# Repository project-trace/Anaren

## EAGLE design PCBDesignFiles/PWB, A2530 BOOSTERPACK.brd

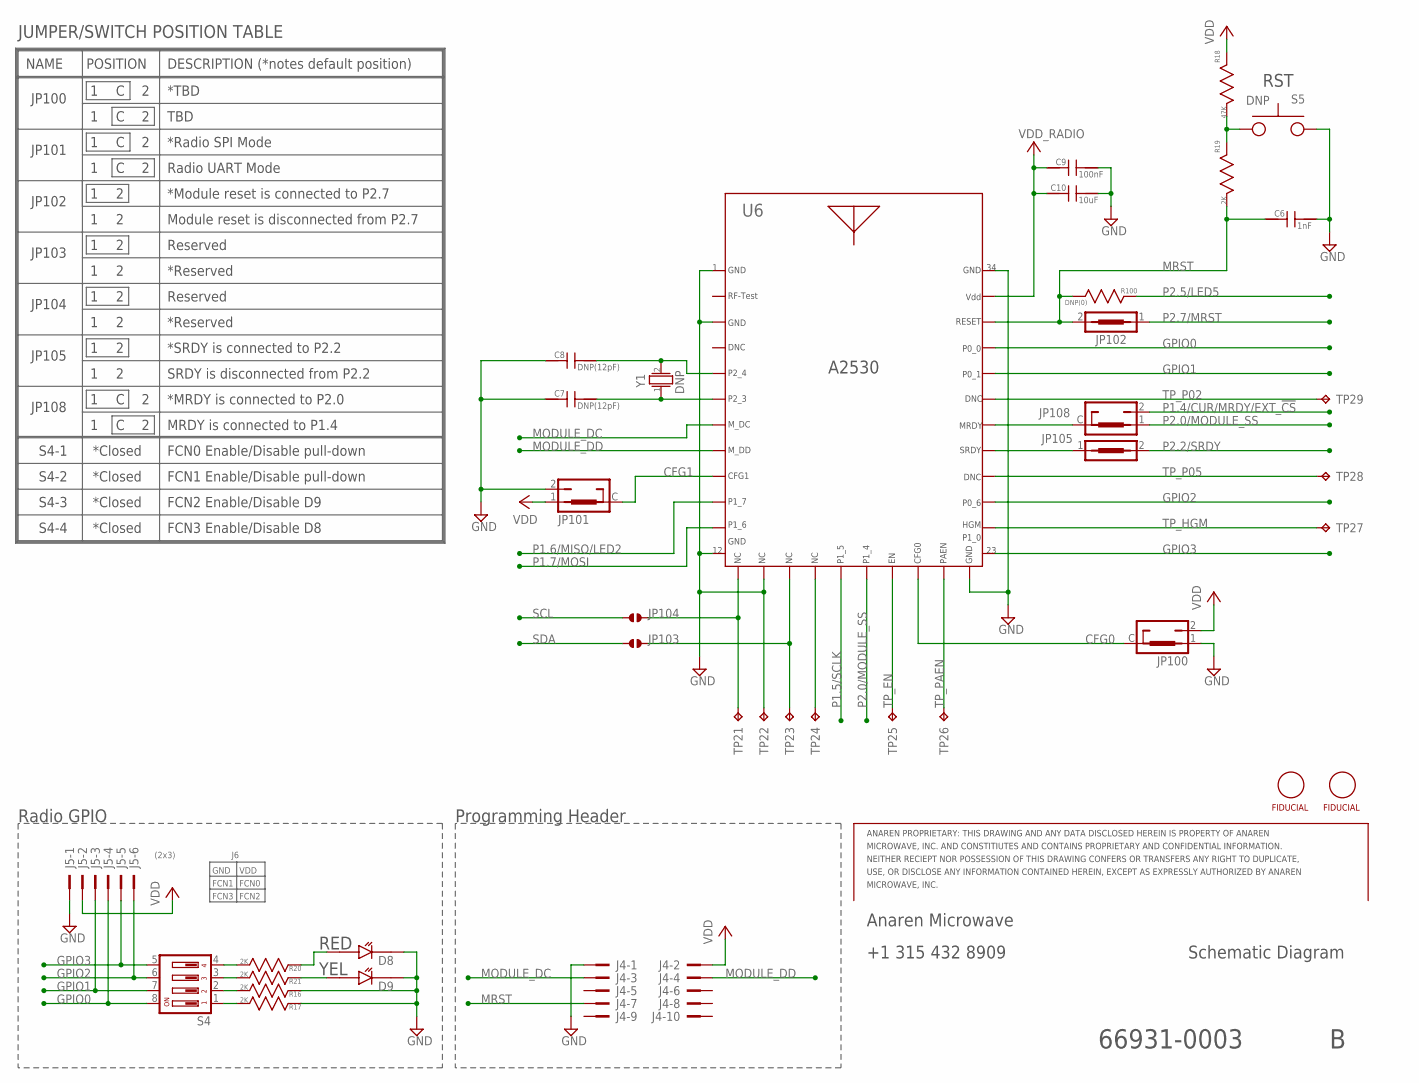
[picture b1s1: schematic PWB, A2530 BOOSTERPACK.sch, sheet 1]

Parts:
C6: 1nF; 0402CAP
C7, C8: DNP(12pF); 0402CAP
C9: 100nF; 0402CAP
C10: 10uF; 0402CAP
D8, D9: LED_SMT_0402; 0402_LED
J4: SAMTEC_SHF-105-01-L-D-TH_NO_SHROUD
J5: PROTO_100MIL_2X3
JP100, JP101, JP108: JP0603_2C_A
JP102, JP105: JP0603_1P_A
JP103, JP104: SOLDER_JUMPER_16MIL; SOLDER_JUMP_16MIL
R16, R17, R19, R20, R21: 2K; RESC1005X40N
R18: 47K; RESC1005X40N
R100: DNP(0); 0603_COMPONENT
S4: DIP_SWITCH_218-4LPSTJ
S5: DNP; SWITCH_B3U-1000P
TP21, TP22, TP23, TP24, TP25, TP26, TP27, TP28, TP29: TP_TH_20MIL_R
U6: CC2530
U$1, U$13: FIDUCIAL0.5MM; FIDUCIAL_0.5MM
Y1: DNP; ABRACON_ABS06

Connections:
CFG0: JP100.C (2), U6.20_GIO2
CFG1: JP101.C (2), U6.9_GIO13
GND: C6.P$2, C7.P$1, C8.P$1, C9.P$2, C10.P$2, D8.2, D9.2, J4.1, J5.1, JP100.1, JP101.2 (3), R16.1, R17.1, S5.2, TP22.P$1, U6.1_GND, U6.3_GND, U6.12_GND, U6.14_USBP, U6.22_GND, U6.34_GND; also elsewhere on the board
GPIO0: J5.4, S4.8, U6.31_HGM
GPIO1: J5.3, S4.7, U6.30_GND
GPIO2: J5.6, S4.6, U6.25_BCLK
GPIO3: J5.5, S4.5, U6.23_RSTN
MODULE_DC: J4.3, U6.7_SDA
MODULE_DD: J4.4, U6.8_GIO12
MRDY: JP108.C (2), U6.28_AD1
MRST: C6.P$1, J4.7, JP102.2, R19.2, R100.1, U6.32_IOVDD; also elsewhere on the board
unnamed: R20.2, S4.4
unnamed: R21.2, S4.3
unnamed: R16.2, S4.2
unnamed: R17.2, S4.1
unnamed: C7.P$2, U6.6_SCL, Y1.1
unnamed: D9.1, R21.1
unnamed: D8.1, R20.1
unnamed: JP104.P2, TP21.P$1, U6.13_USBM
unnamed: JP103.P2, TP23.P$1, U6.15_CSN
unnamed: R18.2, R19.1, S5.1
unnamed: TP24.P$1, U6.16_SCLK
P1.4/CUR/MRDY/EXT_!CS: JP108.2 (3); also elsewhere on the board
P1.5/SCLK: U6.17_MOSI; also elsewhere on the board
P1.6/MISO/LED2: U6.10_PA; also elsewhere on the board
P1.6/MISO/SCL/LED1: C8.P$2, U6.5_VBAT, Y1.2
P1.7/MOSI: U6.11_LNA; also elsewhere on the board
P2.0/MODULE_SS: JP108.1, U6.18_MISO; also elsewhere on the board
P2.2/SRDY: JP105.2; also elsewhere on the board
P2.5/LED5: R100.2; also elsewhere on the board
P2.7/MRST: JP102.1; also elsewhere on the board
SCL: JP104.P1; also elsewhere on the board
SDA: JP103.P1; also elsewhere on the board
SRDY: JP105.1, U6.27_AD0; also elsewhere on the board
TP_EN: TP25.P$1, U6.19_GIO1
TP_HGM: TP27.P$1, U6.24_MCLK
TP_P02: TP29.P$1, U6.29_GIO9/AD2
TP_P05: TP28.P$1, U6.26_WCLK
TP_PAEN: TP26.P$1, U6.21_GIO3
VDD: J4.2, J5.2, JP100.2 (3), JP101.1, R18.1; also elsewhere on the board
VDD_RADIO: C9.P$1, C10.P$1, U6.33_VDD; also elsewhere on the board

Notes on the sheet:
Schematic Diagram
Anaren Microwave
+1 315 432 8909
66931-0003
Programming Header
A2530
RST
YEL
RED
Radio GPIO
JP100
JP101
JP103
JP104
*TBD
TBD
*Radio SPI Mode
Radio UART Mode
Reserved
*Reserved
NAME
POSITION
DESCRIPTION (*notes default position)
JUMPER/SWITCH POSITION TABLE
*Closed
FCN0 Enable/Disable pull-down
S4-1
S4-2
S4-3
S4-4
FCN1 Enable/Disable pull-down
FCN2 Enable/Disable D9
FCN3 Enable/Disable D8
GND
FCN1
FCN3
FCN2
FCN0
VDD
(2x3)

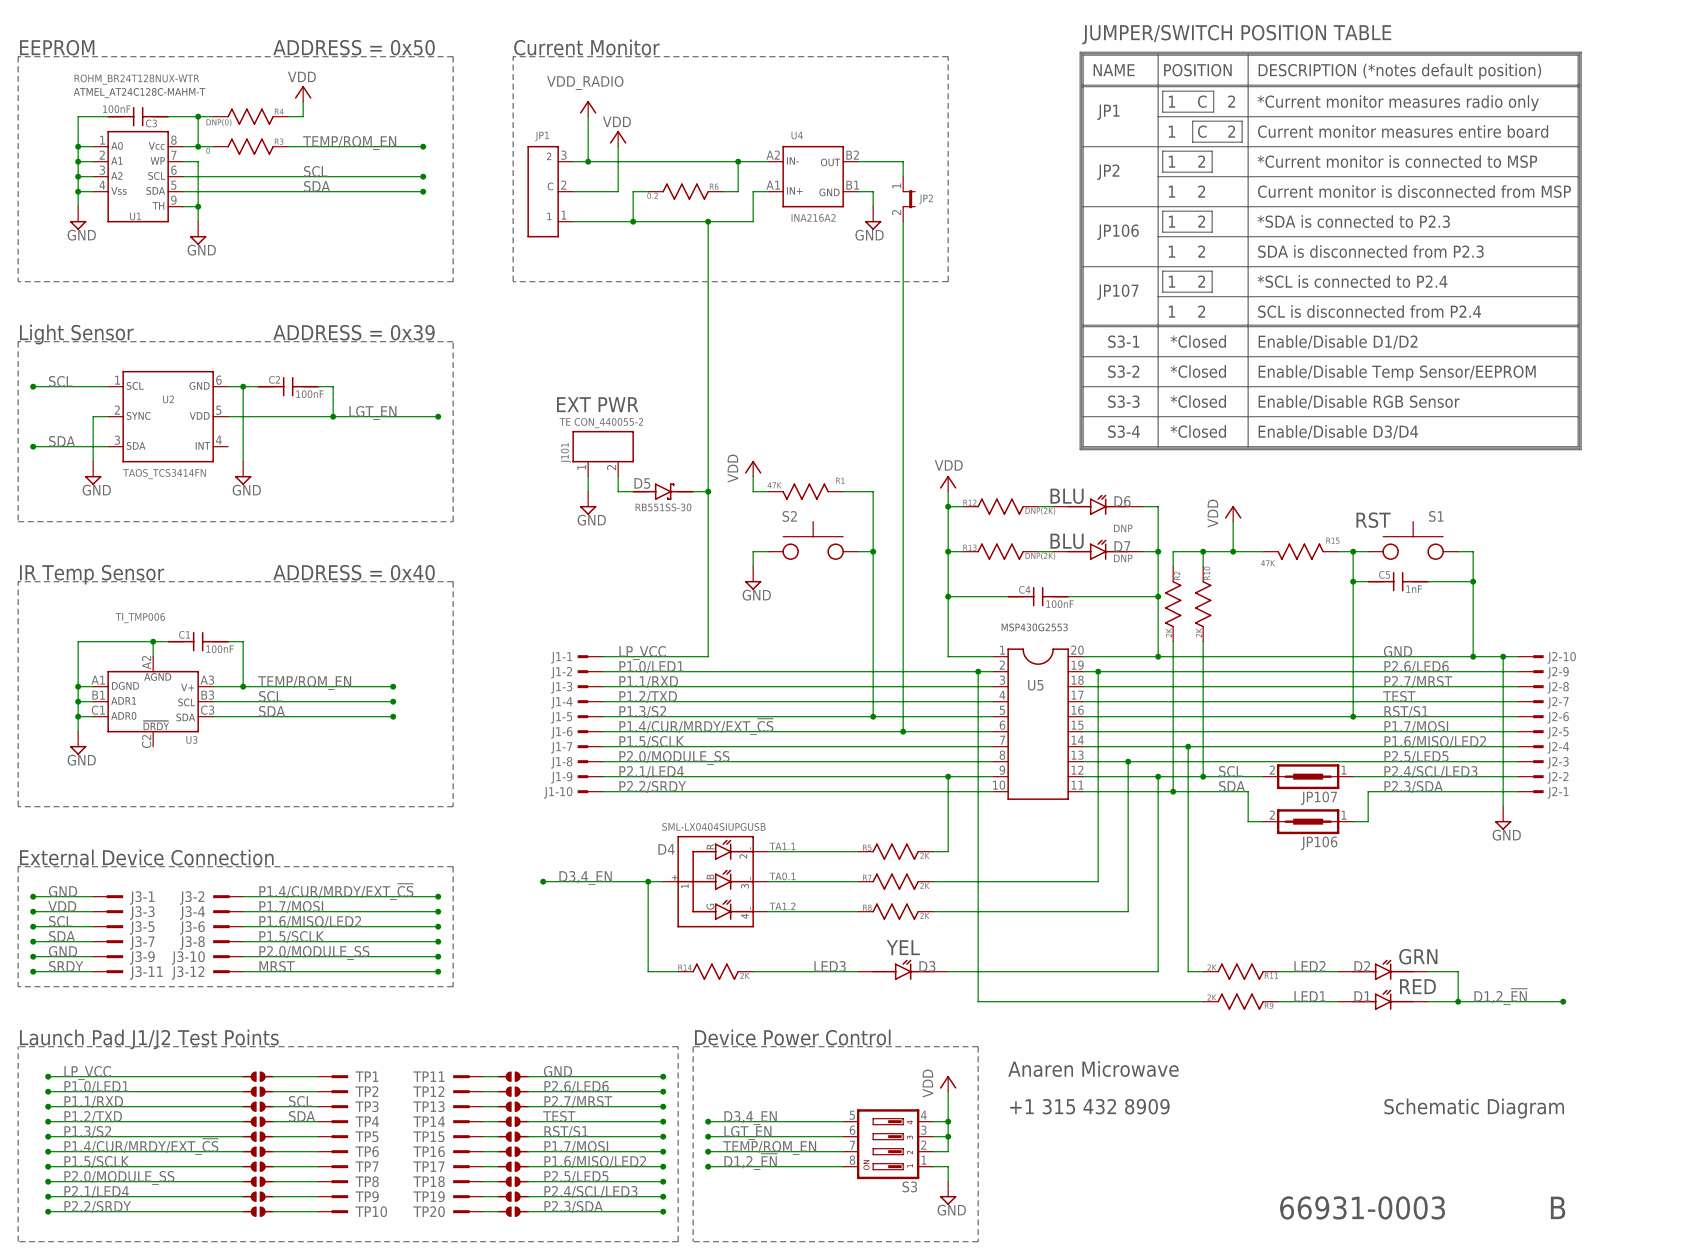
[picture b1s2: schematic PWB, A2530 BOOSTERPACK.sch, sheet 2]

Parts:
C1, C2, C3, C4: 100nF; 0402CAP
C5: 1nF; 0402CAP
D1, D2, D3, D6, D7: LED_SMT_0402; 0402_LED
D4: SML-LX0404SIUPGUSB; SML-LXO404SIUPGUSB
D5: RB551SS-30; 1608_DIODE
J1, J2: TSW-110-02-S-S
J3: PROTO_100MIL_2X6
J101: TE_CONNECTIVITY_HEADER_2POS_2MM_RIGHT_ANGLE_T/H; TE_CONNECTIVITY_HEADER_2POS_2MM_RIGHT_ANGLE_TH
JP1: SAMTEC_TMM-103-XX-X-S
JP2: 2MM_SHUNT_JUMPER; SAMTEC_TMM-102-XX-X-S
JP106, JP107: JP0603_1P_A
R1, R15: 47K; RESC1005X40N
R2, R5, R7, R8, R9, R10, R11, R14: 2K; RESC1005X40N
R3: 0; RESC1005X40N
R4: DNP(0); RESC1005X40N
R6: 0.2; RESC1005X40N
R12, R13: DNP(2K); RESC1005X40N
S1, S2: SWITCH_B3U-1000P
S3: DIP_SWITCH_218-4LPSTJ
TP1, TP2, TP3, TP4, TP5, TP6, TP7, TP8, TP9, TP10, TP11, TP12, TP13, TP14, TP15, TP16, TP17, TP18, TP19, TP20: PROTO
U1: ROHM_BR24T128NUX-WTR; UFDFN8_2.0X3.0
U2: TAOS_TCS3414FN; TAOS_DFP_3.5X2.3
U3: TI_TMP006; BGA-N8
U4: INA216A2; WCSP-4
U5: DIL20
U$2, U$3, U$4, U$5, U$6, U$7, U$8, U$9, U$10, U$11, U$14, U$15, U$16, U$17, U$18, U$19, U$20, U$21, U$22, U$23: SOLDER_JUMPER_16MIL; SOLDER_JUMP_16MIL

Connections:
CURRENT: JP2.1, U4.B2
D1,2_!EN: D1.2, D2.2, S3.8
D3,4_EN: D4.1(+), R14.1, S3.5
GND: C1.P$1, C2.P$1, C3.P$2, C4.P$2, C5.P$2, D6.2, D7.2, J2.10, J3.1, J3.9, J101.1, S1.2, S2.2, S3.1, U1.1, U1.2, U1.3, U1.4, U1.7, U1.9, U2.2, U2.6, U3.A1, U3.A2, U3.B1, U3.C1, U4.B1, U5.20, U$14.P2; also elsewhere on the board
LED1: D1.1, R9.1
LED2: D2.1, R11.1
LED3: D3.1, R14.2
LED4: D4.2(-R), R5.1
LED5: D4.4(-G), R8.1
LED6: D4.3(-B), R7.1
LGT_EN: C2.P$2, S3.6, U2.5
LP_VCC: D5.P$2, J1.1, JP1.1, R6.2, U4.A1, U$2.P1
MRST: J3.12; also elsewhere on the board
unnamed: D6.1, R12.2
unnamed: D7.1, R13.2
unnamed: C3.P$1, R3.2, R4.2, U1.8
unnamed: TP1.1, U$2.P2
unnamed: TP5.1, U$6.P2
unnamed: TP6.1, U$7.P2
unnamed: TP7.1, U$8.P2
unnamed: TP8.1, U$9.P2
unnamed: TP9.1, U$10.P2
unnamed: TP10.1, U$11.P2
unnamed: TP11.1, U$14.P1
unnamed: TP12.1, U$15.P1
unnamed: TP13.1, U$16.P1
unnamed: TP14.1, U$17.P1
unnamed: TP15.1, U$18.P1
unnamed: TP16.1, U$19.P1
unnamed: TP17.1, U$20.P1
unnamed: TP18.1, U$21.P1
unnamed: TP19.1, U$22.P1
unnamed: TP20.1, U$23.P1
unnamed: D5.P$1, J101.2
P1.0/LED1: J1.2, R9.2, U5.2, U$3.P1
P1.1/RXD: J1.3, U5.3, U$4.P1
P1.2/TXD: J1.4, U5.4, U$5.P1
P1.3/S2: J1.5, R1.1, S2.1, U5.5, U$6.P1
P1.4/CUR/MRDY/EXT_!CS: J1.6, J3.2, JP2.2, U5.6, U$7.P1; also elsewhere on the board
P1.5/SCLK: J1.7, J3.8, U5.7, U$8.P1; also elsewhere on the board
P1.6/MISO/LED2: J2.4, J3.6, R11.2, U5.14, U$20.P2; also elsewhere on the board
P1.7/MOSI: J2.5, J3.4, U5.15, U$19.P2; also elsewhere on the board
P2.0/MODULE_SS: J1.8, J3.10, U5.8, U$9.P1; also elsewhere on the board
P2.1/LED4: J1.9, R5.2, U5.9, U$10.P1
P2.2/SRDY: J1.10, U5.10, U$11.P1; also elsewhere on the board
P2.3/SDA: J2.1, JP106.1, U$23.P2
P2.4/SCL/LED3: J2.2, JP107.1, U$22.P2
P2.5/LED5: J2.3, R8.2, U5.13, U$21.P2; also elsewhere on the board
P2.6/LED6: J2.9, R7.2, U5.19, U$15.P2
P2.7/MRST: J2.8, U5.18, U$16.P2; also elsewhere on the board
RST/S1: C5.P$1, J2.6, R15.1, S1.1, U5.16, U$18.P2
SCL: D3.2, J3.5, JP107.2, R10.2, TP3.1, U1.6, U2.1, U3.B3, U5.12, U$4.P2; also elsewhere on the board
SDA: J3.7, JP106.2, R2.2, TP4.1, U1.5, U2.3, U3.C3, U5.11, U$5.P2; also elsewhere on the board
SRDY: J3.11; also elsewhere on the board
STLRS_GND: TP2.1, U$3.P2
TEMP/ROM_EN: C1.P$2, R3.1, S3.7, U3.A3
TEST: J2.7, U5.17, U$17.P2
VDD: C4.P$1, J3.3, JP1.2, R1.2, R2.1, R4.1, R10.1, R12.1, R13.1, R15.2, S3.2, S3.3, S3.4, U5.1; also elsewhere on the board
VDD_RADIO: JP1.3, R6.1, U4.A2; also elsewhere on the board

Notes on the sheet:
Schematic Diagram
Anaren Microwave
+1 315 432 8909
RED
GRN
Light Sensor
MSP430G2553
Current Monitor
RST
IR Temp Sensor
Launch Pad J1/J2 Test Points
ADDRESS = 0x39
ADDRESS = 0x40
JP1
JP2
*Current monitor measures radio only
Current monitor measures entire board
*Current monitor is connected to MSP
Current monitor is disconnected from MSP
NAME
POSITION
DESCRIPTION (*notes default position)
JUMPER/SWITCH POSITION TABLE
EXT PWR
YEL
EEPROM
External Device Connection
ADDRESS = 0x50
66931-0003
TE CON_440055-2
Device Power Control
JP106
JP107
*SDA is connected to P2.3
SDA is disconnected from P2.3
*SCL is connected to P2.4
SCL is disconnected from P2.4
S3-1
S3-2
Enable/Disable D1/D2

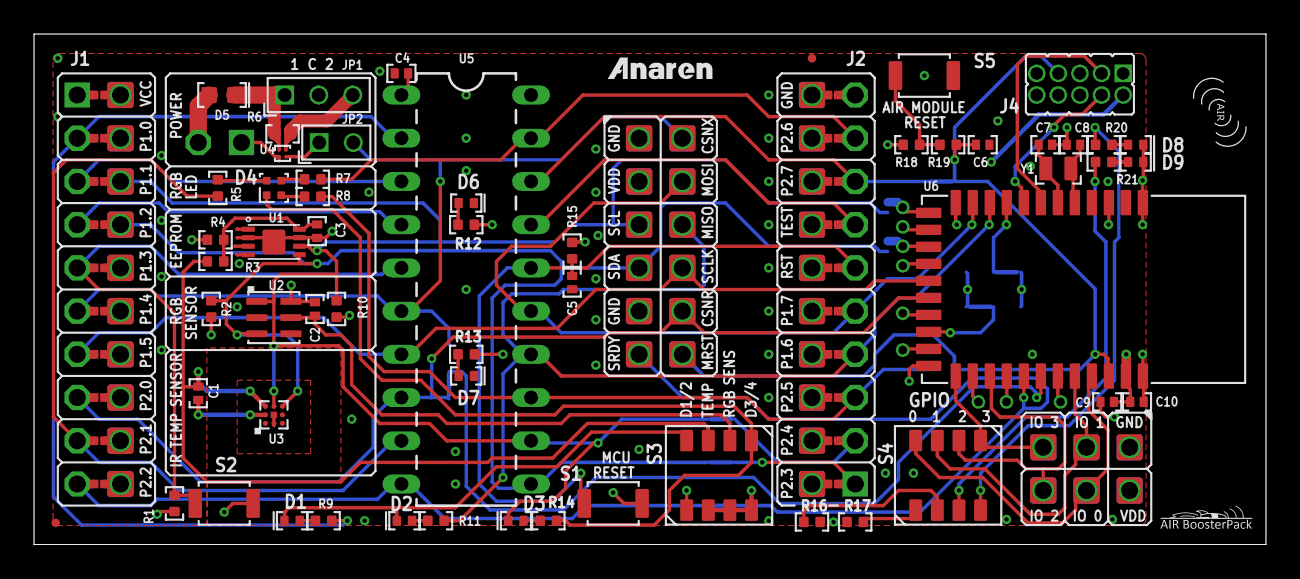
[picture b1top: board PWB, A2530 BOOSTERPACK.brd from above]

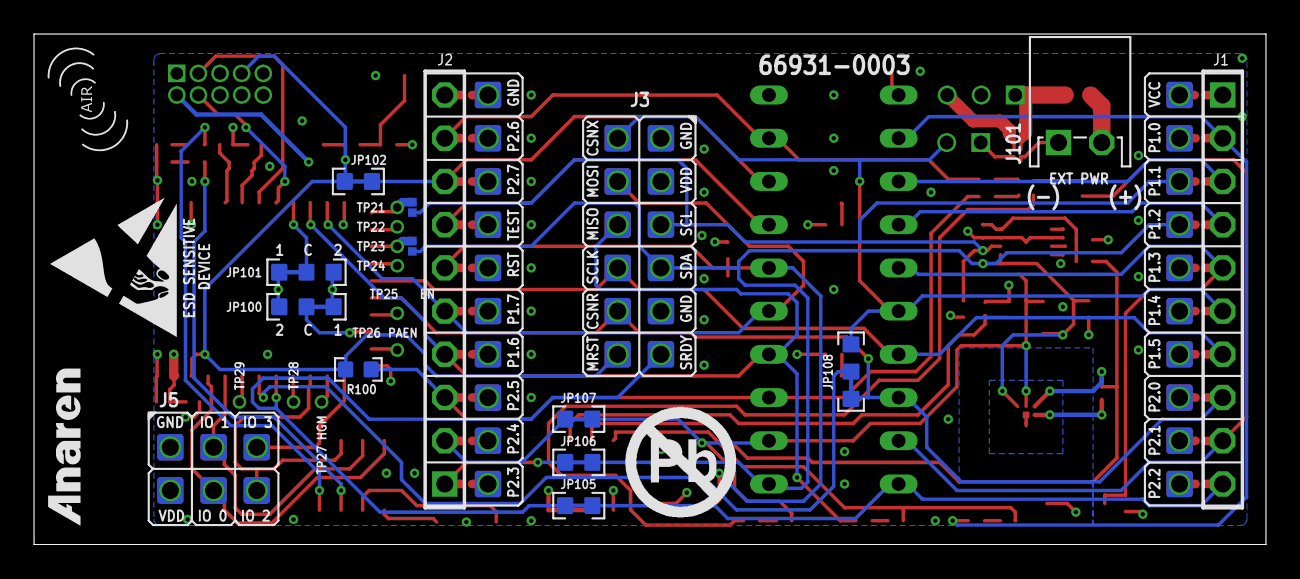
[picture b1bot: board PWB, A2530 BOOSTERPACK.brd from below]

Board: 4 copper layers, 72.4 x 30.0 mm, 129 parts (21 on the bottom side), 85 nets.

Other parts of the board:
DRILEGEND: DRILEGEND
U$12: ANAREN_LOGO_SCALE_0.2
U$24: LAUNCHPAD_HALF_ROCKET_SCALE_0.5
U$25: AIR_LOGO_SCALE_0.1
U$100: ANAREN_LOGO_SCALE_0.3
U$101: AIR_LOGO_SCALE_0.15
U$102: ESD_LOGO_SCALE_0.2
U$103: PB-FREE_LOGO_SCALE_1.0

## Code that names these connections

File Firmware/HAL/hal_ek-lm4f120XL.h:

/*
* @file hal_ek-lm4f120XL.h
*
* @brief public methods for hal_ek-lm4f120XL.c Adapted from hal_gw1.h.
*
* $Rev: 1568 $
* $Author: dsmith $
* $Date: 2012-09-24 17:16:29 -0700 (Mon, 24 Sep 2012) $
*
* @section support Support
* Please refer to the wiki at http://teslacontrols.com/mw/ for more information. Additional support
* is available via email at the following addresses:
* - Questions on how to use the product: AIR@anaren.com
* - Feature requests, comments, and improvements:  featurerequests@teslacontrols.com
* - Consulting engagements: sales@teslacontrols.com
*
* @section license License
* Copyright (c) 2012 Tesla Controls. All rights reserved. This Software may only be used with an 
* Anaren A2530E24AZ1, A2530E24CZ1, A2530R24AZ1, or A2530R24CZ1 module. Redistribution and use in 
* source and binary forms, with or without modification, are subject to the Software License 
* Agreement in the file "anaren_eula.txt"
* 
* YOU FURTHER ACKNOWLEDGE AND AGREE THAT THE SOFTWARE AND DOCUMENTATION ARE PROVIDED AS IS 
* WITHOUT WARRANTY OF ANY KIND, EITHER EXPRESS OR IMPLIED, INCLUDING WITHOUT LIMITATION, ANY 
* WARRANTY OF MERCHANTABILITY, TITLE, NON-INFRINGEMENT AND FITNESS FOR A PARTICULAR PURPOSE. IN NO 
* EVENT SHALL ANAREN MICROWAVE OR TESLA CONTROLS BE LIABLE OR OBLIGATED UNDER CONTRACT, NEGLIGENCE, 
* STRICT LIABILITY, CONTRIBUTION, BREACH OF WARRANTY, OR OTHER LEGAL EQUITABLE THEORY ANY DIRECT OR 
* INDIRECT DAMAGES OR EXPENSE INCLUDING BUT NOT LIMITED TO ANY INCIDENTAL, SPECIAL, INDIRECT, 
* PUNITIVE OR CONSEQUENTIAL DAMAGES, LOST PROFITS OR LOST DATA, COST OF PROCUREMENT OF SUBSTITUTE 
* GOODS, TECHNOLOGY, SERVICES, OR ANY CLAIMS BY THIRD PARTIES (INCLUDING BUT NOT LIMITED TO ANY 
* DEFENSE THEREOF), OR OTHER SIMILAR COSTS.
* 
*/

#ifndef HAL_EK_LM4F120XL_H
#define HAL_EK_LM4F120XL_H

#include "inc/hw_memmap.h"
#include "inc/hw_types.h"
#include "driverlib/interrupt.h"
#include "driverlib/gpio.h"
#include "driverlib/sysctl.h"
#include "utils/uartstdio.h"
#include <stdint.h>

/** Redirect printf to the Stellaris UARTprintf() implementation. Requires including utils/uartstdio.c */
#define printf UARTprintf

//
//  CORE METHODS REQUIRED FOR ZIGBEE MODULE INTERFACE
//
void halInit();
void delayMs(uint16_t ms);
void halSpiInitModule();
void spiWrite(uint8_t *bytes, uint8_t numBytes);
int16_t toggleLed(uint8_t whichLed);
int16_t setLed(uint8_t led);
int16_t clearLed(uint8_t led);
void clearLeds();

#define ON_NETWORK_LED          2
#define NETWORK_FAILURE_LED     1
#define SEND_MESSAGE_LED        3

//
//  OTHER
//
void halSetWakeupFlags(uint16_t wakeupFlagsToSet);
void halRgbLedPwmInit();
void halRgbSetLeds(uint8_t red, uint8_t blue, uint8_t green);
// For RGB LED interface consistency:
//RGB LED:
#define RGB_LED_PWM_OFF                	0x00
#define RGB_LED_PWM_PERIOD              0xFF

uint8_t halUartBusy();
uint16_t getCurrentSensor();
uint8_t buttonIsPressed(uint8_t button);



/** Get the processor clock frequency */
#define GET_MCLK_FREQ() (SysCtlClockGet())
#define TICKS_PER_MS	25000			// used in FAST_PROCESSOR option of zm_phy
#define TICKS_PER_US (TICKS_PER_MS / 1000)
//#define WAIT_WHILE_SPI_BUSY()  while ((HWREG(SSI0_BASE + SSI_O_SR)) & SSI_SR_BSY)   //wait while busy

// Buttons
#define ANY_BUTTON          0xFF
#define BUTTON_0            0
#define BUTTON_1            1
#define BUTTON_2            2

/* Peripherals:
LED0 - Red LED on BoosterPack, PB5
LED1 - Blue of RGB LED on BoosterPack, PB2
Can also use the Green LED on BoosterPack, but it's shared with MISO
Note: For pretty colors we're using the RGB LED on the Stellaris LaunchPad, not the one on the BoosterPack,
since the one on the LaunchPad is controlled by hardware PWM.
*/

//Module RST = PE0
//Module MRDY = CS = PA5
//Module SRDY = PA7
//PRECONDITIONS: GPIO PORTS HAVE BEEN ENABLED & PINS WERE CONFIGURED: RST, MRDY as outputs; SRDY as input
#define RADIO_ON()                  ( GPIOPinWrite(GPIO_PORTE_BASE, GPIO_PIN_0, GPIO_PIN_0) )
#define RADIO_OFF()                 ( GPIOPinWrite(GPIO_PORTE_BASE, GPIO_PIN_0, 0) )
#define SPI_SS_SET()                ( GPIOPinWrite(GPIO_PORTA_BASE, GPIO_PIN_5, 0) ) 	//MRDY tied to CS in hardware?
#define SPI_SS_CLEAR()              ( GPIOPinWrite(GPIO_PORTA_BASE, GPIO_PIN_5, GPIO_PIN_5) )
#define SRDY_IS_HIGH()              (GPIOPinRead(GPIO_PORTA_BASE, GPIO_PIN_7) & GPIO_PIN_7)
#define SRDY_IS_LOW()               (~(GPIOPinRead(GPIO_PORTA_BASE, GPIO_PIN_7)) & GPIO_PIN_7)

#define HAL_ENABLE_INTERRUPTS()		IntMasterEnable()
#define HAL_DISABLE_INTERRUPTS()	IntMasterDisable()

#define DEBUG_ON()
#define DEBUG_OFF()

#define HAL_SLEEP()     ( SysCtlSleep() )
//#define HAL_WAKEUP()

int16_t calibrateVlo();
int16_t initTimer(uint8_t seconds);
#define NO_WAKEUP                   0
#define WAKEUP_AFTER_TIMER          1
#define WAKEUP_AFTER_BUTTON         2


//#define XTAL                        25000000L


#endif

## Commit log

2015-11-10 Anaren set up
